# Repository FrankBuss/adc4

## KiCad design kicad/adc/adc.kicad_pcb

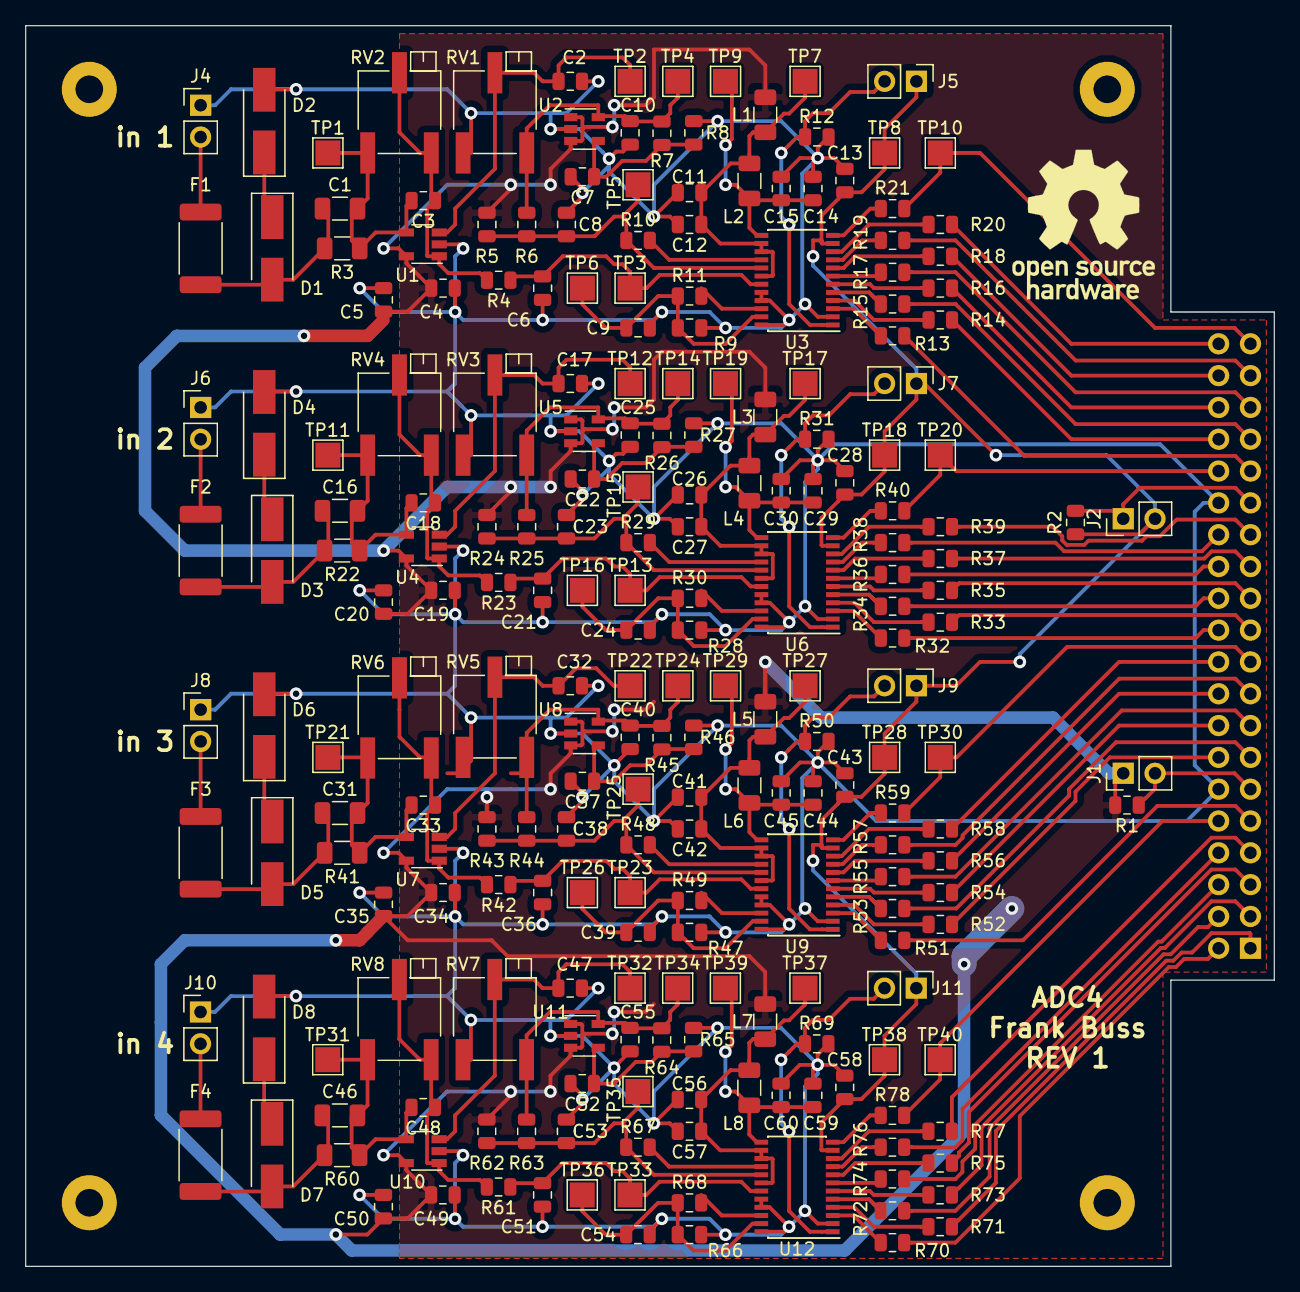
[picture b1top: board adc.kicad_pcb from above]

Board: 2 copper layers, 99.7 x 99.1 mm, 229 parts (1 on the bottom side), 141 nets.

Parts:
C1, C16, C31, C46: n.p.; C_1206_3216Metric
C2, C4, C12, C13, C15, C17, C19, C27, C28, C30, C32, C34, C42, C43, C45, C47, C49, C57, C58, C60: 100n; C_0805_2012Metric
C3, C18, C33, C48: 0.5p; C_0805_2012Metric
C5, C11, C14, C20, C26, C29, C35, C41, C44, C50, C56, C59: 10u; C_0805_2012Metric
C6, C21, C36, C51: 47p; C_0805_2012Metric
C7, C22, C37, C52: 470p; C_0805_2012Metric
C8, C9, C10, C23, C24, C25, C38, C39, C40, C53, C54, C55: 1u; C_0805_2012Metric
D1, D2, D3, D4, D5, D6, D7, D8: SM4T15AY; D_SMA_Handsoldering
F1, F2, F3, F4: Fuse; Fuse_2512_6332Metric
J1: +5V Isense; PinHeader_1x02_P2.54mm_Vertical
J2: +3.3V Isense; PinHeader_1x02_P2.54mm_Vertical
J3: DE10 Nano GPIO 0/1; PinSocket_2x20_P2.54mm_Vertical
J4, J6, J8, J10: analog in; PinHeader_1x02_P2.54mm_Vertical
J5, J7, J9, J11: disable jumper; PinHeader_1x02_P2.54mm_Vertical
L1, L2, L3, L4, L5, L6, L7, L8: BLM31KN801SN1L; L_1206_3216Metric
R1, R2, R6, R9, R25, R28, R44, R47, R63, R66: 0; R_0805_2012Metric
R3, R22, R41, R60: 150k; R_1206_3216Metric
R4, R13, R14, R15, R16, R17, R18, R19, R20, R21, R23, R32, R33, R34, R35, R36, R37, R38, R39, R40, R42, R51, R52, R53, R54, R55, R56, R57, R58, R59, R61, R70, R71, R72, R73, R74, R75, R76, R77, R78: 33; R_0805_2012Metric
R5, R10, R11, R24, R29, R30, R43, R48, R49, R62, R67, R68: n.p.; R_0805_2012Metric
R7, R26, R45, R64: 4k5; R_0805_2012Metric
R8, R12, R27, R31, R46, R50, R65, R69: 10k; R_0805_2012Metric
RV1, RV2, RV3, RV4, RV5, RV6, RV7, RV8: 50k; Potentiometer_Bourns_3269P_Horizontal
TP1, TP2, TP3, TP4, TP5, TP6, TP7, TP8, TP9, TP10, TP11, TP12, TP13, TP14, TP15, TP16, TP17, TP18, TP19, TP20, TP21, TP22, TP23, TP24, TP25, TP26, TP27, TP28, TP29, TP30, TP31, TP32, TP33, TP34, TP35, TP36, TP37, TP38, TP39, TP40: TestPoint; TestPoint_Pad_2.0x2.0mm
U1, U4, U7, U10: ADA4891; TSOT-23-5
U2, U5, U8, U11: MIC5219-adj; SOT-23-5
U3, U6, U9, U12: ADC1175-50; TSSOP-24_4.4x7.8mm_P0.65mm

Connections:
+3V3: C13.1, C28.1, C43.1, C58.1, J2.2, J5.1, J7.1, J9.1, J11.1, R2.1, TP8.1, TP18.1, TP28.1, TP38.1, U3.11, U6.11, U9.11, U12.11
+5V: C4.1, C5.1, C19.1, C20.1, C34.1, C35.1, C49.1, C50.1, J1.1, L1.2, L3.2, L5.2, L7.2, R1.2, R5.2, R24.2, R43.2, R62.2, U1.5, U2.1, U2.3, U4.5, U5.1, U5.3, U7.5, U8.1, U8.3, U10.5, U11.1, U11.3
/ADC1-CLK: J3.39, R21.2, TP10.1
/ADC1-D0: J3.31, R13.2
/ADC1-D1: J3.34, R14.2
/ADC1-D2: J3.33, R15.2
/ADC1-D3: J3.36, R16.2
/ADC1-D4: J3.35, R17.2
/ADC1-D5: J3.38, R18.2
/ADC1-D6: J3.37, R19.2
/ADC1-D7: J3.40, R20.2
/ADC2-CLK: J3.32, R40.2, TP20.1
/ADC2-D0: J3.22, R32.2
/ADC2-D1: J3.21, R33.2
/ADC2-D2: J3.24, R34.2
/ADC2-D3: J3.23, R35.2
/ADC2-D4: J3.26, R36.2
/ADC2-D5: J3.25, R37.2
/ADC2-D6: J3.28, R38.2
/ADC2-D7: J3.27, R39.2
/ADC3-CLK: J3.10, R78.2, TP40.1
/ADC3-D0: J3.2, R70.2
/ADC3-D1: J3.1, R71.2
/ADC3-D2: J3.4, R72.2
/ADC3-D3: J3.3, R73.2
/ADC3-D4: J3.6, R74.2
/ADC3-D5: J3.5, R75.2
/ADC3-D6: J3.8, R76.2
/ADC3-D7: J3.7, R77.2
/ADC4-CLK: J3.19, R59.2, TP30.1
/ADC4-D0: J3.9, R51.2
/ADC4-D1: J3.14, R52.2
/ADC4-D2: J3.13, R53.2
/ADC4-D3: J3.16, R54.2
/ADC4-D4: J3.15, R55.2
/ADC4-D5: J3.18, R56.2
/ADC4-D6: J3.17, R57.2
/ADC4-D7: J3.20, R58.2
GND: C2.2, C4.2, C5.2, C6.2, C7.2, C8.2, C9.2, C10.2, C11.2, C12.2, C13.2, C14.1, C15.1, C17.2, C19.2, C20.2, C21.2, C22.2, C23.2, C24.2, C25.2, C26.2, C27.2, C28.2, C29.1, C30.1, C32.2, C34.2, C35.2, C36.2, C37.2, C38.2, C39.2, C40.2, C41.2, C42.2, C43.2, C44.1, C45.1, C47.2, C49.2, C50.2, C51.2, C52.2, C53.2, C54.2, C55.2, C56.2, C57.2, C58.2, C59.1, C60.1, D2.2, D4.2, D6.2, D8.2, J3.12, J3.30, J4.1, J6.1, J8.1, J10.1, R8.1, R9.1, R12.2, R27.1, R28.1, R31.2, R46.1, R47.1, R50.2, R65.1, R66.1, R69.2, RV1.3, RV3.3, RV5.3, RV7.3, U1.2, U2.2, U3.2, U3.20, U3.21, U3.24, U4.2, U5.2, U6.2, U6.20, U6.21, U6.24, U7.2, U8.2, U9.2, U9.20, U9.21, U9.24, U10.2, U11.2, U12.2, U12.20, U12.21, U12.24
unnamed: C1.1, C3.2, R3.2, RV2.3, TP1.1, U1.4
unnamed: C1.2, D1.2, F1.1, R3.1
unnamed: C2.1, RV1.2, TP2.1, U1.3
unnamed: C3.1, R4.2, RV2.1, RV2.2, U1.1
unnamed: C6.1, R4.1, TP3.1, U3.19
unnamed: C7.1, R7.1, R8.2, U2.4
unnamed: C8.1, R5.1, R6.2, R10.1, TP5.1, U3.17
unnamed: C9.1, R9.2, R11.1, TP6.1, U3.23
unnamed: C10.1, R6.1, R7.2, RV1.1, TP4.1, U2.5
unnamed: C11.1, C12.1, L1.1, L2.2, TP7.1, U3.14, U3.15, U3.18
unnamed: C14.2, C15.2, L2.1, TP9.1, U3.13
unnamed: C16.1, C18.2, R22.2, RV4.3, TP11.1, U4.4
unnamed: C16.2, D3.2, F2.1, R22.1
unnamed: C17.1, RV3.2, TP12.1, U4.3
unnamed: C18.1, R23.2, RV4.1, RV4.2, U4.1
unnamed: C21.1, R23.1, TP13.1, U6.19
unnamed: C22.1, R26.1, R27.2, U5.4
unnamed: C23.1, R24.1, R25.2, R29.1, TP15.1, U6.17
unnamed: C24.1, R28.2, R30.1, TP16.1, U6.23
unnamed: C25.1, R25.1, R26.2, RV3.1, TP14.1, U5.5
unnamed: C26.1, C27.1, L3.1, L4.2, TP17.1, U6.14, U6.15, U6.18
unnamed: C29.2, C30.2, L4.1, TP19.1, U6.13
unnamed: C31.1, C33.2, R41.2, RV6.3, TP21.1, U7.4
unnamed: C31.2, D5.2, F3.1, R41.1
unnamed: C32.1, RV5.2, TP22.1, U7.3
unnamed: C33.1, R42.2, RV6.1, RV6.2, U7.1
unnamed: C36.1, R42.1, TP23.1, U9.19
unnamed: C37.1, R45.1, R46.2, U8.4
unnamed: C38.1, R43.1, R44.2, R48.1, TP25.1, U9.17
unnamed: C39.1, R47.2, R49.1, TP26.1, U9.23
unnamed: C40.1, R44.1, R45.2, RV5.1, TP24.1, U8.5
unnamed: C41.1, C42.1, L5.1, L6.2, TP27.1, U9.14, U9.15, U9.18
unnamed: C44.2, C45.2, L6.1, TP29.1, U9.13
unnamed: C46.1, C48.2, R60.2, RV8.3, TP31.1, U10.4
unnamed: C46.2, D7.2, F4.1, R60.1
unnamed: C47.1, RV7.2, TP32.1, U10.3
unnamed: C48.1, R61.2, RV8.1, RV8.2, U10.1
unnamed: C51.1, R61.1, TP33.1, U12.19
unnamed: C52.1, R64.1, R65.2, U11.4
unnamed: C53.1, R62.1, R63.2, R67.1, TP35.1, U12.17
unnamed: C54.1, R66.2, R68.1, TP36.1, U12.23
unnamed: C55.1, R63.1, R64.2, RV7.1, TP34.1, U11.5
unnamed: C56.1, C57.1, L7.1, L8.2, TP37.1, U12.14, U12.15, U12.18
unnamed: C59.2, C60.2, L8.1, TP39.1, U12.13
unnamed: D1.1, D2.1
unnamed: D3.1, D4.1
unnamed: D5.1, D6.1
unnamed: D7.1, D8.1
unnamed: F1.2, J4.2
unnamed: F2.2, J6.2
unnamed: F3.2, J8.2
unnamed: F4.2, J10.2
unnamed: J1.2, J3.11, R1.1
unnamed: J2.1, J3.29, R2.2
unnamed: J5.2, R12.1, U3.1
unnamed: J7.2, R31.1, U6.1
unnamed: J9.2, R50.1, U9.1
unnamed: J11.2, R69.1, U12.1
unnamed: R10.2, U3.16
unnamed: R11.2, U3.22
unnamed: R13.1, U3.3
unnamed: R14.1, U3.4
unnamed: R15.1, U3.5
unnamed: R16.1, U3.6
unnamed: R17.1, U3.7
unnamed: R18.1, U3.8
unnamed: R19.1, U3.9
unnamed: R20.1, U3.10
unnamed: R21.1, U3.12
unnamed: R29.2, U6.16
unnamed: R30.2, U6.22
unnamed: R32.1, U6.3
unnamed: R33.1, U6.4
unnamed: R34.1, U6.5
unnamed: R35.1, U6.6
unnamed: R36.1, U6.7
unnamed: R37.1, U6.8
unnamed: R38.1, U6.9
unnamed: R39.1, U6.10
unnamed: R40.1, U6.12
unnamed: R48.2, U9.16
unnamed: R49.2, U9.22
unnamed: R51.1, U9.3
unnamed: R52.1, U9.4
unnamed: R53.1, U9.5
unnamed: R54.1, U9.6
unnamed: R55.1, U9.7
unnamed: R56.1, U9.8
unnamed: R57.1, U9.9
unnamed: R58.1, U9.10
unnamed: R59.1, U9.12
unnamed: R67.2, U12.16
unnamed: R68.2, U12.22
unnamed: R70.1, U12.3
unnamed: R71.1, U12.4
unnamed: R72.1, U12.5
unnamed: R73.1, U12.6
unnamed: R74.1, U12.7
unnamed: R75.1, U12.8
unnamed: R76.1, U12.9
unnamed: R77.1, U12.10
unnamed: R78.1, U12.12

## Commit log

2018-12-04 initial version
2018-12-04 fixed OpAmp power supply and added another decoupling capacitor
2018-12-05 PCB routed
2018-12-05 PDF files updated
2018-12-06 first version, ordered at JLCPCB
2018-12-28 first working FPGA version with Python test script
2018-12-28 current schematic
2018-12-29 sampling at falling edge and multi channel oscilloscope test
2019-01-06 DDR3 RAM sample storage implemented
2019-01-06 samplerate divider added, and serial port speed increased to 1 Mbaud/s, with CRC8 checksum and reading from arbitrary start addresses in case of transfer errors
2019-01-06 bugfixing
